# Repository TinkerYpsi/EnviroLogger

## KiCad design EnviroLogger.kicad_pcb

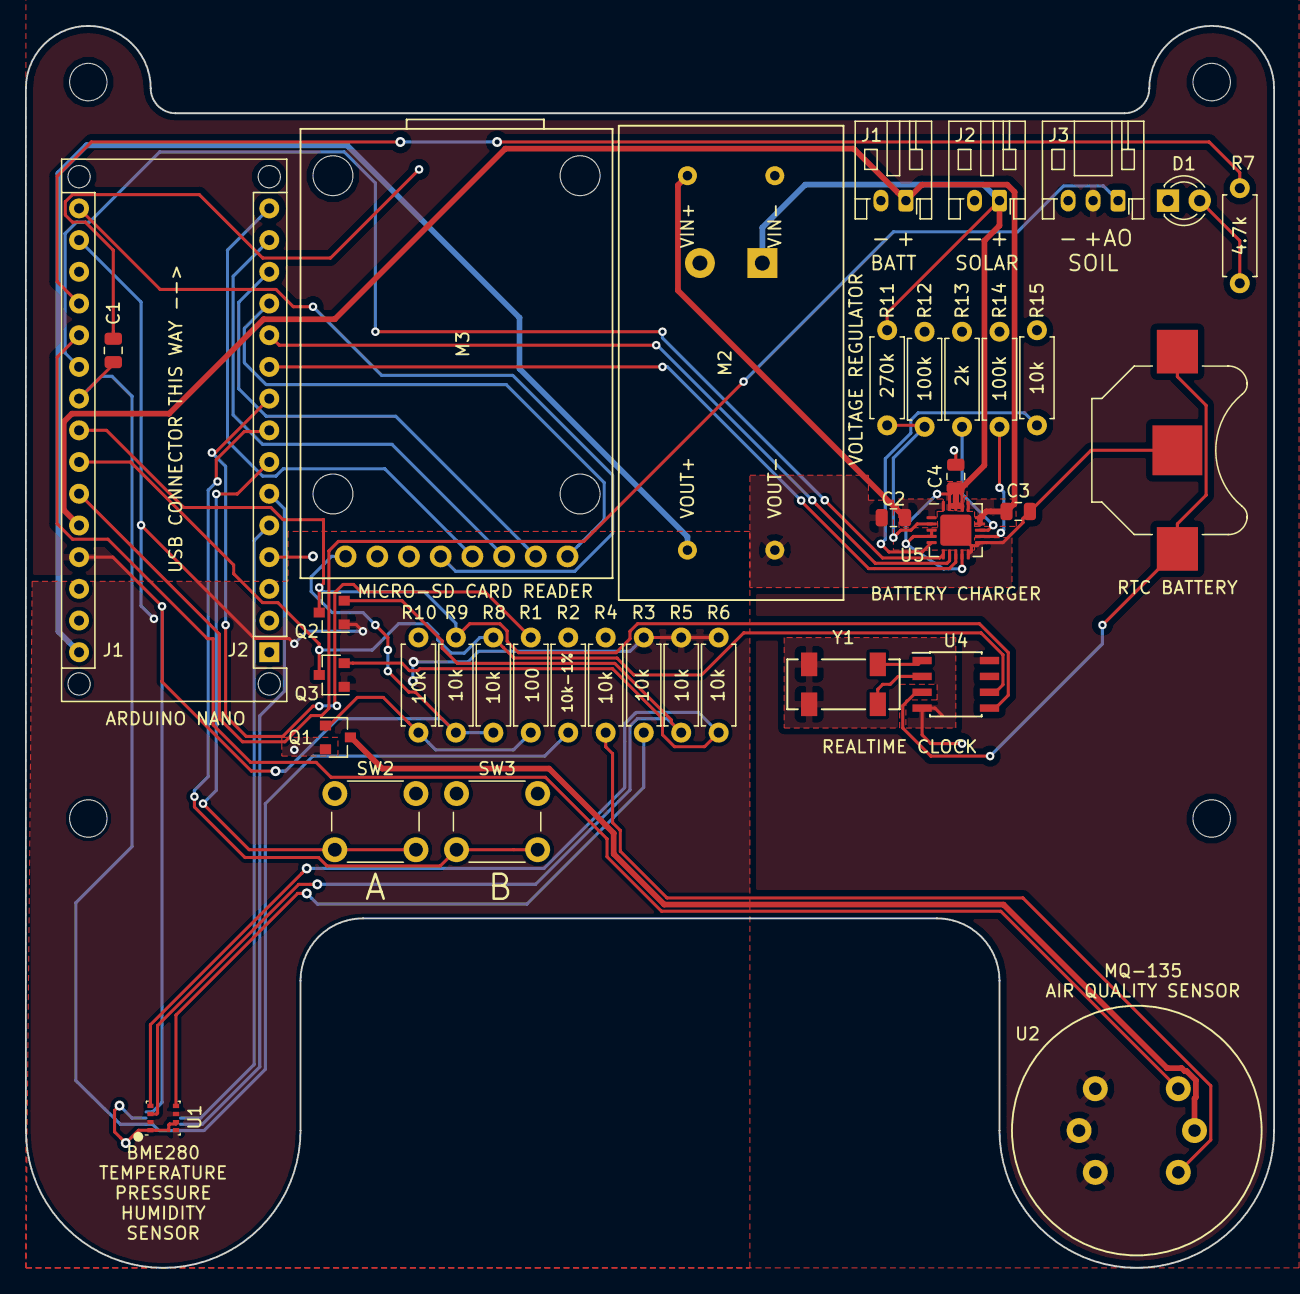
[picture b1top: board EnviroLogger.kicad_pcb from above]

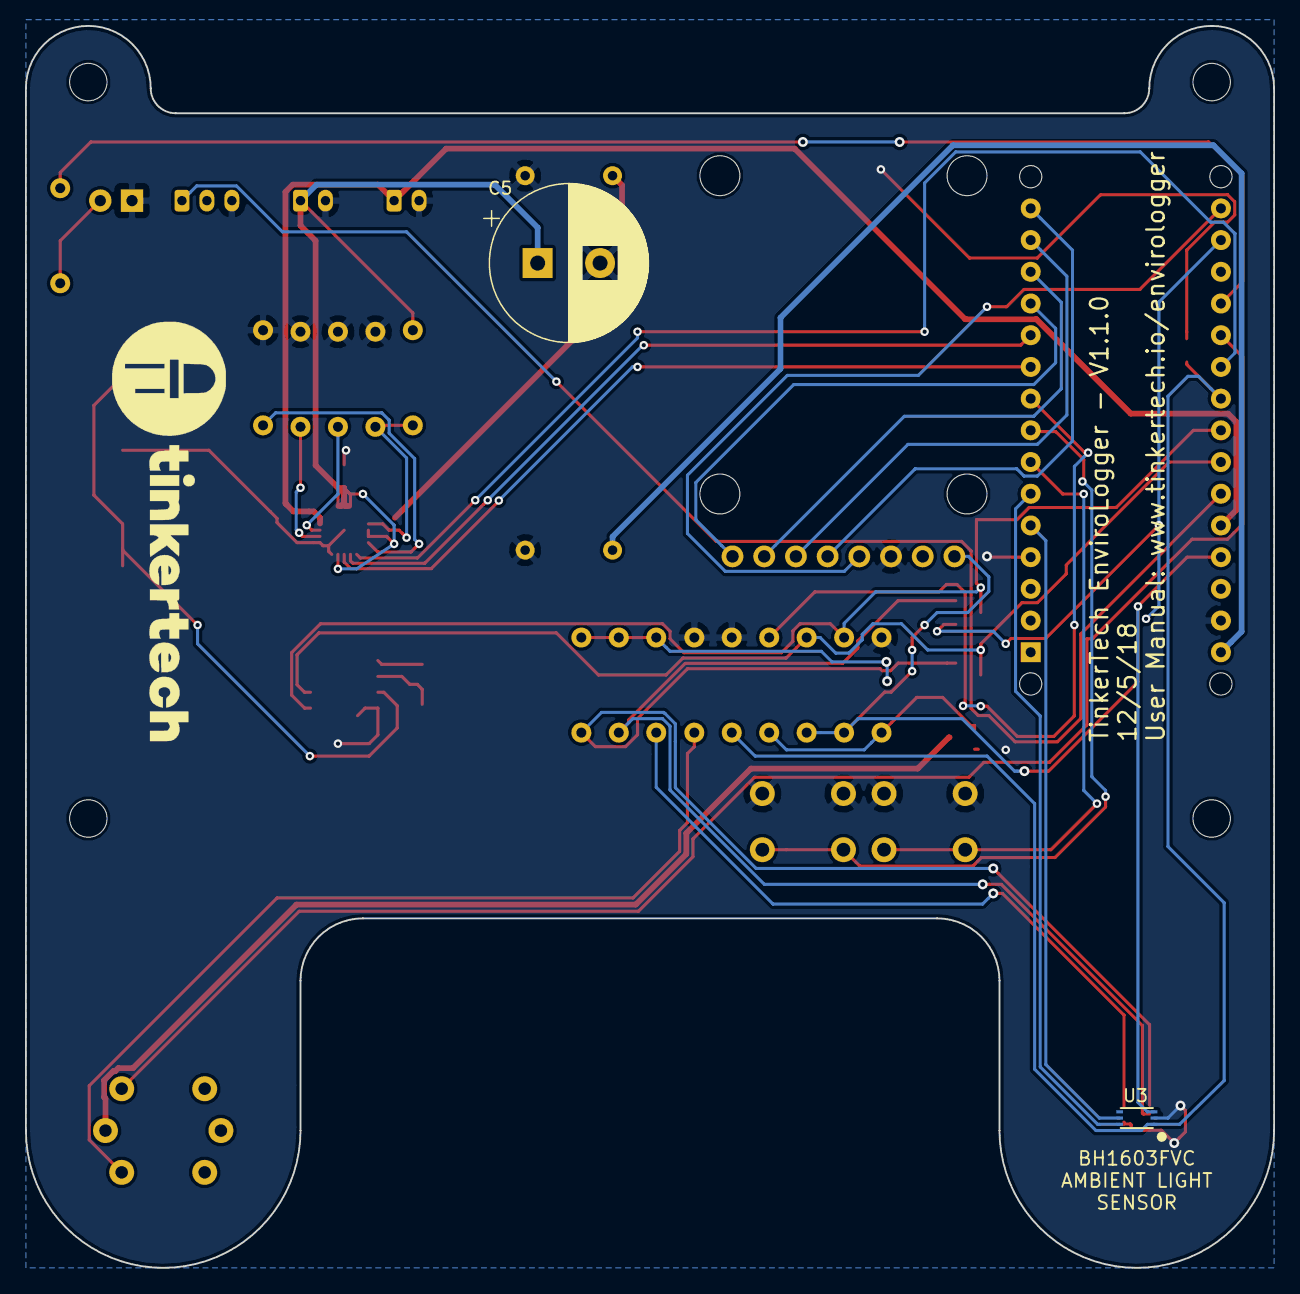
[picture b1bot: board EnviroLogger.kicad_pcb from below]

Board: 2 copper layers, 100.0 x 99.5 mm, 44 parts (3 on the bottom side), 40 nets.

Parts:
A1: Arduino_Nano_v3.x; Arduino_Nano_WithMountingHoles
BT1: Battery_Cell; BatteryHolder_Keystone_3000_1x12mm
C1, C2, C3, C4: 10uF; C_0805_2012Metric
C5: 4700uF; CP_Radial_D12.5mm_P5.00mm
D1: LED; LED_D3.0mm
H1, H2, H3, H4: MountingHole; MountingHole_3mm
J1, J2: Conn_01x02_Male; JST_PH_S2B-PH-K_1x02_P2.00mm_Horizontal
J3: Conn_01x03_Male; JST_PH_S3B-PH-K_1x03_P2.00mm_Horizontal
M2: MT3608_Boost_Regulator
M3: RobotDyn_MicroSD_Card_Reader
Q1: DMN6140L; SOT-23
Q2, Q3: BSS138; SOT-23
R1: 100; R_Axial_DIN0207_L6.3mm_D2.5mm_P7.62mm_Horizontal
R2: 10k-1%; R_Axial_DIN0207_L6.3mm_D2.5mm_P7.62mm_Horizontal
R3, R4, R5, R6, R8, R9, R10, R15: 10k; R_Axial_DIN0207_L6.3mm_D2.5mm_P7.62mm_Horizontal
R7: 4.7k; R_Axial_DIN0207_L6.3mm_D2.5mm_P7.62mm_Horizontal
R11: 270k; R_Axial_DIN0207_L6.3mm_D2.5mm_P7.62mm_Horizontal
R12, R14: 100k; R_Axial_DIN0207_L6.3mm_D2.5mm_P7.62mm_Horizontal
R13: 2k; R_Axial_DIN0207_L6.3mm_D2.5mm_P7.62mm_Horizontal
SLK1: TT_Logo; TinkerTech-Logo_34.4x10mm_SilkScreen
SW2, SW3: SW_Push; SW_PUSH_6mm_H4.3mm
U1: BME280; Bosch_LGA-8_2.5x2.5mm_P0.65mm_ClockwisePinNumbering
U2: MQ-135
U3: BH1603FVC; WSOF6
U4: DS1307ZN+; SOIC-8_3.9x4.9mm_P1.27mm
U5: MCP73871; QFN-20-1EP_4x4mm_P0.5mm_EP2.5x2.5mm
Y1: Crystal_GND23; Crystal_SMD_CardinalComponents_CPFB-4Pin_8.7x3.7mm

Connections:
+3V3: A1.17, Q2.1, Q3.1, R3.1, R5.2, R6.2, U1.2, U1.6, U1.8
+5V: A1.27, J3.2, M3.8, R8.2, R9.2, U2.1, U2.2, U2.3, U3.3, U4.8
BATT+: A1.26, C3.1, J1.1, U5.14, U5.15, U5.16
BUTTON_1: A1.7, SW2.2
BUTTON_2: A1.8, SW3.2
CARD_DETECT: A1.12, M3.1
CHARGER_VOUT: C2.1, M2.4, U5.1, U5.20
GAIN_CTR_1: A1.5, U3.5
GAIN_CTR_2: A1.6, U3.6
GND: A1.4, A1.29, BT1.2, C1.2, C2.2, C3.2, C4.2, C5.2, D1.1, J1.2, J2.2, J3.3, M2.2, M2.3, M3.6, Q1.2, R2.2, R4.2, R10.1, R12.1, R13.1, R14.1, R15.2, SW2.1, SW3.1, U1.1, U1.7, U3.2, U4.4, U5.10, U5.11, U5.21, Y1.2, Y1.3
INDICATOR_LED: A1.19, R7.1
LIGHT_SENSE_CURRENT: A1.22, C1.1, R2.1, U3.1
MQ-150-GND: Q1.3, U2.5
MQ-150_OUT: A1.20, U2.6
MQ-150_Toggle: A1.9, R1.2
NANO_VIN: A1.30, M2.1
unnamed: BT1.1, U4.3
unnamed: D1.2, R7.2
unnamed: Q1.1, R1.1, R10.2
unnamed: R3.2, U1.5
unnamed: R4.1, U2.4
unnamed: R11.1, R12.2, U5.2
unnamed: R13.2, U5.13
unnamed: R14.2, U5.12
unnamed: R15.1, U5.5
unnamed: U4.1, Y1.1
unnamed: U4.2, Y1.4
SCK_3.3V: Q3.2, R6.1, U1.4
SCK_5V: A1.24, Q3.3, R8.1, U4.6
SDA_3.3V: Q2.2, R5.1, U1.3
SDA_5V: A1.23, Q2.3, R9.1, U4.5
SOIL_MOISTURE_OUT: A1.25, J3.1
SOLAR+: C4.1, C5.1, J2.1, R11.2, U5.3, U5.4, U5.9, U5.17, U5.18, U5.19
SPI_CLK: A1.16, M3.5
SPI_MISO: A1.15, M3.4
SPI_MOSI: A1.14, M3.3
SPI_SS: A1.13, M3.2
STAT1: A1.10, U5.8
STAT2: A1.11, U5.7
~PG: A1.21, U5.6

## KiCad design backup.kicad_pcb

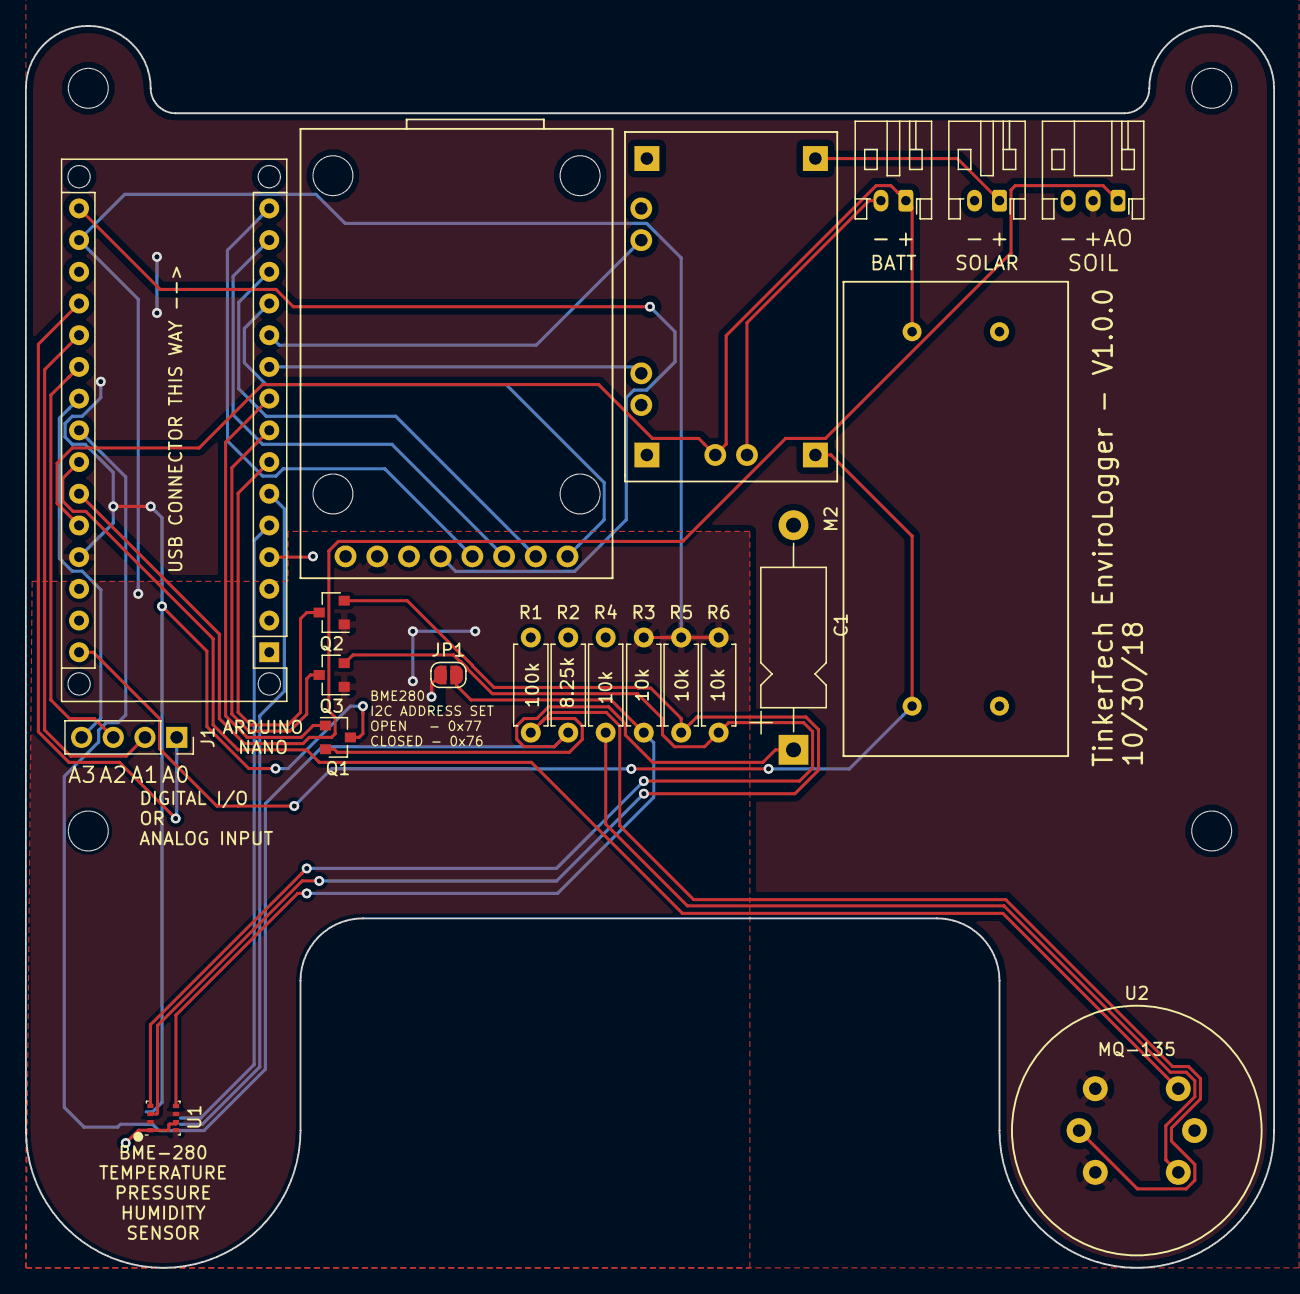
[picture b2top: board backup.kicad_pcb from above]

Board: 2 copper layers, 100.0 x 99.5 mm, 22 parts (1 on the bottom side), 31 nets.

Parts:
A1: Arduino_Nano_v3.x; Arduino_Nano_WithMountingHoles
C1: 12uF; CP_Axial_L11.0mm_D5.0mm_P18.00mm_Horizontal
J1: Conn_01x04_Female; PinSocket_1x04_P2.54mm_Vertical
J3: Conn_01x03_Male; JST_PH_S3B-PH-K_1x03_P2.00mm_Horizontal
J4, J5: Conn_01x02_Male; JST_PH_S2B-PH-K_1x02_P2.00mm_Horizontal
JP1: SolderJumper_2_Open; SolderJumper-2_P1.3mm_Open_RoundedPad1.0x1.5mm
M1: RobotDyn_Li-Ion_Charger_W-Protection
M2: MT3608_Boost_Regulator
M3: RobotDyn_MicroSD_Card_Reader
Q1, Q2, Q3: BSS138; SOT-23
R1: 100k; R_Axial_DIN0207_L6.3mm_D2.5mm_P7.62mm_Horizontal
R2: 8.25k; R_Axial_DIN0207_L6.3mm_D2.5mm_P7.62mm_Horizontal
R3, R4, R5, R6: 10k; R_Axial_DIN0207_L6.3mm_D2.5mm_P7.62mm_Horizontal
U1: BME280; Bosch_LGA-8_2.5x2.5mm_P0.65mm_ClockwisePinNumbering
U2: MQ-135
U3: BH1603FVC; WSOF6

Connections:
+3V3: A1.17, M3.7, Q2.1, Q3.1, R3.1, R5.2, R6.2, U1.2, U1.6, U1.8
+5V: A1.27, J3.2, Q1.3, U2.1, U2.3, U3.3
BATT+: A1.26, J4.1, M1.8, M2.4
BATT-: J4.2, M1.9
CARD_DETECT: A1.12, M3.1
CHG_ACTIVE: A1.10, M1.5
CHG_STBY: A1.11, M1.4
GAIN_CTR_1: A1.5, U3.5
GAIN_CTR_2: A1.6, U3.6
GND: A1.4, A1.29, C1.2, J3.3, J5.2, JP1.2, M1.2, M1.3, M1.6, M1.7, M2.2, M2.3, M3.6, R1.2, R2.2, R4.2, U1.1, U1.7, U2.5, U3.2
LIGHT_SENSE_CURRENT: A1.23, C1.1, R2.1, U3.1
MQ-150_OUT: A1.24, U2.6
MQ-150_Toggle: A1.9, Q1.1
NANO_VIN: A1.30, M1.10, M2.1
unnamed: A1.19, J1.1
unnamed: A1.20, J1.2
unnamed: A1.21, J1.3
unnamed: A1.22, J1.4
unnamed: JP1.1, R3.2, U1.5
unnamed: Q1.2, R1.1, U2.2
unnamed: R4.1, U2.4
SCK_3.3V: Q3.2, R6.1, U1.4
SCK_5V: A1.8, Q3.3
SDA_3.3V: Q2.2, R5.1, U1.3
SDA_5V: A1.7, Q2.3
SOIL_MOISTURE_OUT: A1.25, J3.1
SOLAR+: J5.1, M1.1
SPI_CLK: A1.16, M3.5
SPI_MISO: A1.15, M3.4
SPI_MOSI: A1.14, M3.3
SPI_SS: A1.13, M3.2

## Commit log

2018-11-13 :octocat: Added .gitattributes & .gitignore files
2018-11-14 Updated to V1.1.0
    Fixed many issues:
    - Battery polarity was reversed
    - I2C SDA and SCL were on the wrong Nano pins
    - Added missing pull-up resistor on 5V side of I2C level shifter
    - Added a real time clock to the design
    - Fixed boost regulator wiring
2018-12-05 Update to V1.0.2
    Fixed battery grounding issue
2019-02-18 Updated to V1.1.0
    Added solar charging circuitry
